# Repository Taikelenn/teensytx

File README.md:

Project in active development, this README will be updated as development progresses

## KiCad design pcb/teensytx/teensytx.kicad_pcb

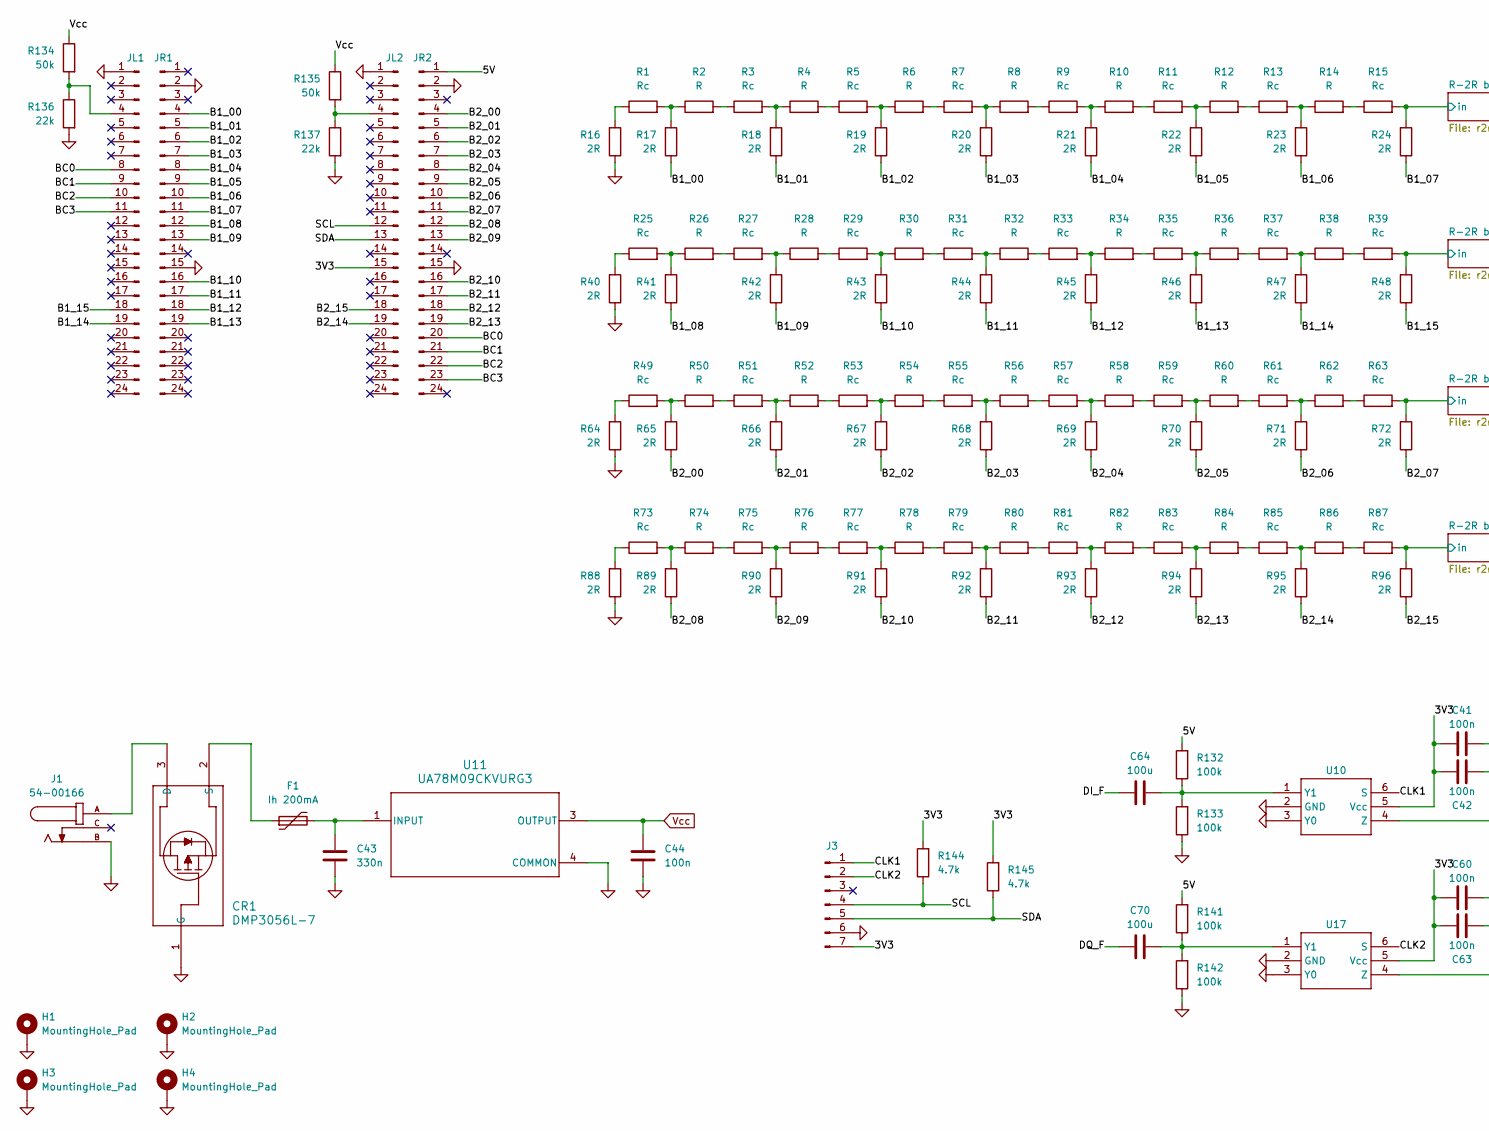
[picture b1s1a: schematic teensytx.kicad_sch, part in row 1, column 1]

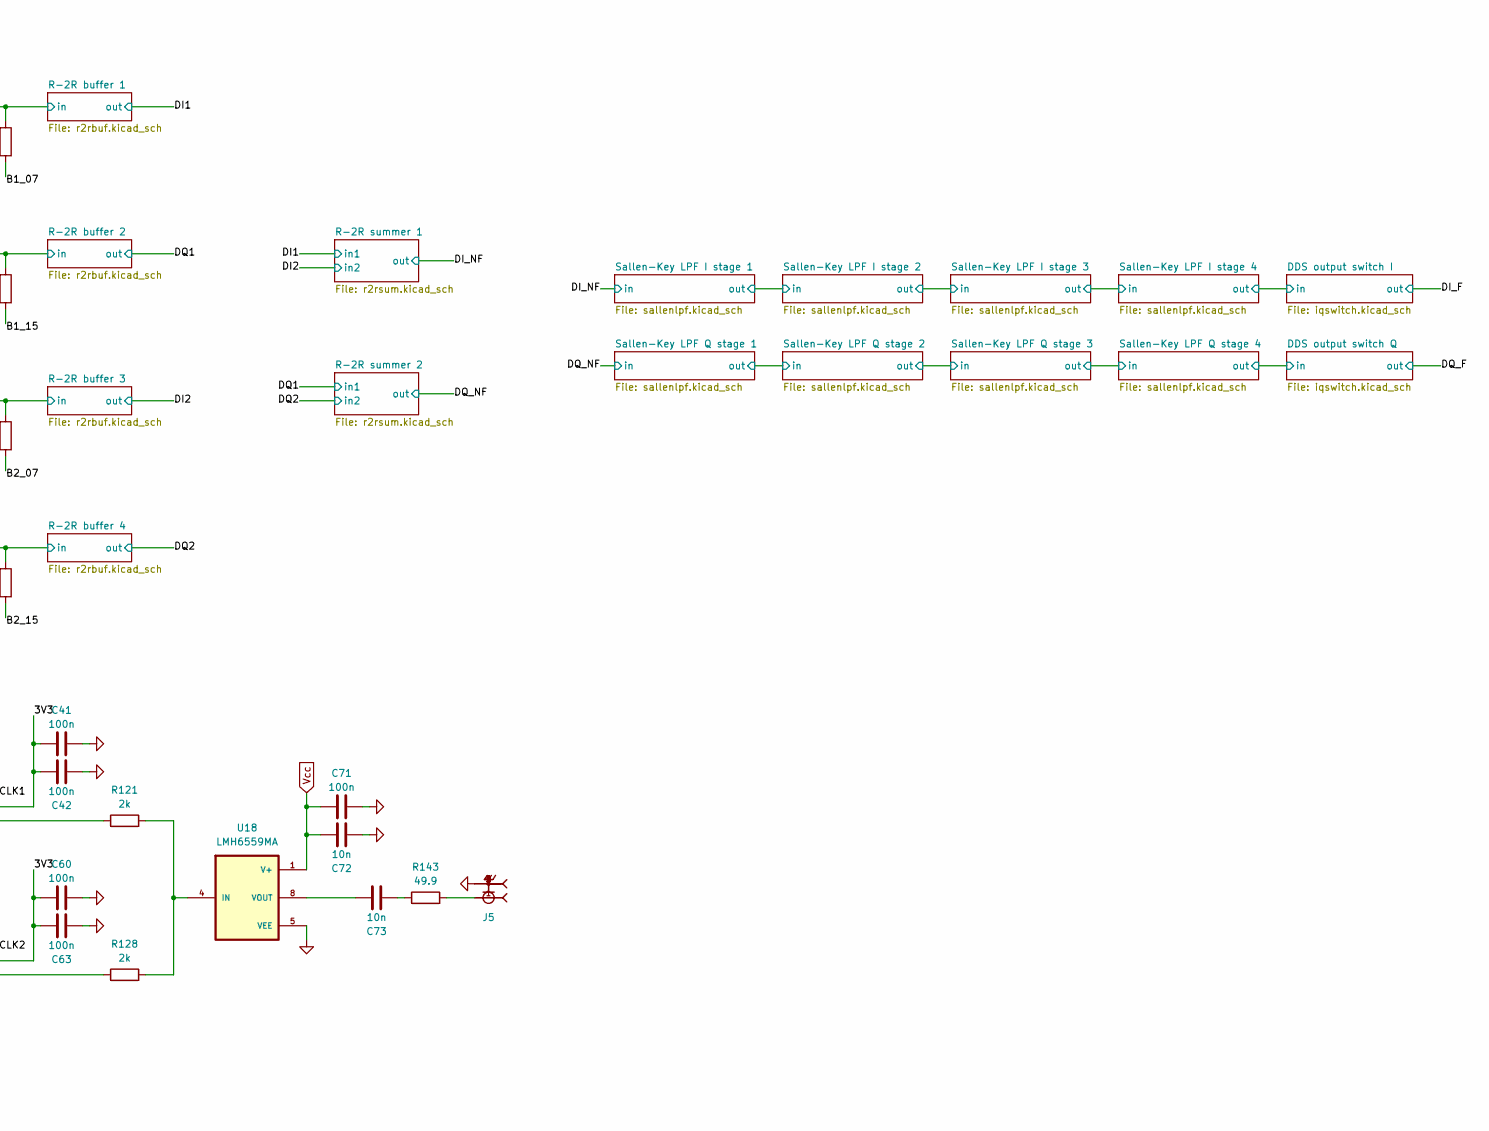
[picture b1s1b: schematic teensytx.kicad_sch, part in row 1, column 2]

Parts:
C41, C42, C44, C60, C63, C71: 100n; C_0805_2012Metric_Pad1.18x1.45mm_HandSolder
C43: 330n; C_0805_2012Metric_Pad1.18x1.45mm_HandSolder
C64, C70: 100u; C_0805_2012Metric_Pad1.18x1.45mm_HandSolder
C72, C73: 10n; C_0805_2012Metric_Pad1.18x1.45mm_HandSolder
CR1: DMP3056L-7; DIODE3_DESD1CAN2SOQ-7_DIO
F1: Ih 200mA; RESC3216X125N
H1, H2, H3, H4: MountingHole_Pad; MountingHole_3.2mm_M3_Pad
J1: 54-00166; TENSILITY_54-00166; PARTREV A
J3: Conn_01x07_Pin; PinHeader_1x07_P2.54mm_Vertical
J5: SMA-J-P-X-RA-TH1; SAMTEC_SMA-J-P-X-RA-TH1; PARTREV K
JL1, JL2: Conn_01x24_Pin; PinHeader_1x24_P2.54mm_Vertical
JR1, JR2: Conn_01x24_Pin; PinHeader_1x24_P2.54mm_Vertical
R1, R3, R5, R7, R9, R11, R13, R15, R25, R27, R29, R31, R33, R35, R37, R39, R49, R51, R53, R55, R57, R59, R61, R63, R73, R75, R77, R79, R81, R83, R85, R87: Rc; R_0805_2012Metric_Pad1.20x1.40mm_HandSolder
R2, R4, R6, R8, R10, R12, R14, R26, R28, R30, R32, R34, R36, R38, R50, R52, R54, R56, R58, R60, R62, R74, R76, R78, R80, R82, R84, R86: R; R_0805_2012Metric_Pad1.20x1.40mm_HandSolder
R16, R17, R18, R19, R20, R21, R22, R23, R24, R40, R41, R42, R43, R44, R45, R46, R47, R48, R64, R65, R66, R67, R68, R69, R70, R71, R72, R88, R89, R90, R91, R92, R93, R94, R95, R96: 2R; R_0805_2012Metric_Pad1.20x1.40mm_HandSolder
R121, R128: 2k; R_0805_2012Metric_Pad1.20x1.40mm_HandSolder
R132, R133, R141, R142: 100k; R_0805_2012Metric_Pad1.20x1.40mm_HandSolder
R134, R135: 50k; R_0805_2012Metric_Pad1.20x1.40mm_HandSolder
R136, R137: 22k; R_0805_2012Metric_Pad1.20x1.40mm_HandSolder
R143: 49.9; R_1206_3216Metric_Pad1.30x1.75mm_HandSolder
R144, R145: 4.7k; R_0805_2012Metric_Pad1.20x1.40mm_HandSolder
U10, U17: TSOP-6_1.65x3.05mm_P0.95mm
U11: UA78M09CKVURG3; KVU0003A_N
U18: LMH6559MA; SOIC127P599X175-8N

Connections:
/3V3: C41.2, C42.2, C60.2, C63.2, J3.7, JL2.15, R144.2, R145.2, U10.5 (Vcc), U17.5 (Vcc)
/5V: JR2.1, R132.2, R141.2
/B1_00: JR1.4, R17.1
/B1_01: JR1.5, R18.1
/B1_02: JR1.6, R19.1
/B1_03: JR1.7, R20.1
/B1_04: JR1.8, R21.1
/B1_05: JR1.9, R22.1
/B1_06: JR1.10, R23.1
/B1_07: JR1.11, R24.1
/B1_08: JR1.12, R41.1
/B1_09: JR1.13, R42.1
/B1_10: JR1.16, R43.1
/B1_11: JR1.17, R44.1
/B1_12: JR1.18, R45.1
/B1_13: JR1.19, R46.1
/B1_14: JL1.19, R47.1
/B1_15: JL1.18, R48.1
/B2_00: JR2.4, R65.1
/B2_01: JR2.5, R66.1
/B2_02: JR2.6, R67.1
/B2_03: JR2.7, R68.1
/B2_04: JR2.8, R69.1
/B2_05: JR2.9, R70.1
/B2_06: JR2.10, R71.1
/B2_07: JR2.11, R72.1
/B2_08: JR2.12, R89.1
/B2_09: JR2.13, R90.1
/B2_10: JR2.16, R91.1
/B2_11: JR2.17, R92.1
/B2_12: JR2.18, R93.1
/B2_13: JR2.19, R94.1
/B2_14: JL2.19, R95.1
/B2_15: JL2.18, R96.1
/BC0: JL1.8, JR2.20
/BC1: JL1.9, JR2.21
/BC2: JL1.10, JR2.22
/BC3: JL1.11, JR2.23
/CLK1: J3.1, U10.6 (S)
/CLK2: J3.2, U17.6 (S)
/DI_F: C64.1; also elsewhere on the board
/DQ_F: C70.1; also elsewhere on the board
/R-2R buffer 1/in: R15.2, R24.2; also elsewhere on the board
/R-2R buffer 2/in: R39.2, R48.2; also elsewhere on the board
/R-2R buffer 3/in: R63.2, R72.2; also elsewhere on the board
/R-2R buffer 4/in: R87.2, R96.2; also elsewhere on the board
/SCL: J3.4, JL2.12, R144.1
/SDA: J3.5, JL2.13, R145.1
GND: C41.1, C42.1, C43.2, C44.2, C60.1, C63.1, C71.2, C72.2, CR1.1 (G), H1.1, H2.1, H3.1, H4.1, J1.B, J3.6, J5.2, J5.3, J5.4, J5.5, JL1.1, JL2.1, JR1.2, JR1.15, JR2.2, JR2.15, R16.1, R40.1, R64.1, R88.1, R133.1, R136.2, R137.2, R142.1, U10.2 (GND), U10.3 (Y0), U11.4 (COMMON), U17.2 (GND), U17.3 (Y0), U18.5 (VEE); also elsewhere on the board
unnamed: C73.2, R143.1
unnamed: CR1.3 (D), J1.A
unnamed: CR1.2 (S), F1.1
unnamed: J5.1, R143.2
unnamed: JL1.4, R134.2, R136.1
unnamed: JL2.4, R135.2, R137.1
unnamed: R1.1, R16.2
unnamed: R1.2, R2.1, R17.2
unnamed: R2.2, R3.1
unnamed: R4.2, R5.1
unnamed: R6.2, R7.1
unnamed: R8.2, R9.1
unnamed: R9.2, R10.1, R21.2
unnamed: R10.2, R11.1
unnamed: R11.2, R12.1, R22.2
unnamed: R12.2, R13.1
unnamed: R13.2, R14.1, R23.2
unnamed: R14.2, R15.1
unnamed: R3.2, R4.1, R18.2
unnamed: R5.2, R6.1, R19.2
unnamed: R7.2, R8.1, R20.2
unnamed: R25.1, R40.2
unnamed: R25.2, R26.1, R41.2
unnamed: R26.2, R27.1
unnamed: R27.2, R28.1, R42.2
unnamed: R28.2, R29.1
unnamed: R29.2, R30.1, R43.2
unnamed: R30.2, R31.1
unnamed: R31.2, R32.1, R44.2
unnamed: R32.2, R33.1
unnamed: R33.2, R34.1, R45.2
unnamed: R34.2, R35.1
unnamed: R35.2, R36.1, R46.2
unnamed: R36.2, R37.1
unnamed: R37.2, R38.1, R47.2
unnamed: R38.2, R39.1
unnamed: R49.1, R64.2
unnamed: R49.2, R50.1, R65.2
unnamed: R50.2, R51.1
unnamed: R51.2, R52.1, R66.2
unnamed: R52.2, R53.1
unnamed: R53.2, R54.1, R67.2
unnamed: R54.2, R55.1
unnamed: R55.2, R56.1, R68.2
unnamed: R56.2, R57.1
unnamed: R57.2, R58.1, R69.2
unnamed: R58.2, R59.1
unnamed: R59.2, R60.1, R70.2
unnamed: R60.2, R61.1
unnamed: R61.2, R62.1, R71.2
unnamed: R62.2, R63.1
unnamed: R73.1, R88.2
unnamed: R73.2, R74.1, R89.2
unnamed: R74.2, R75.1
unnamed: R75.2, R76.1, R90.2
unnamed: R76.2, R77.1
unnamed: R77.2, R78.1, R91.2
unnamed: R78.2, R79.1
unnamed: R79.2, R80.1, R92.2
unnamed: R80.2, R81.1
unnamed: R81.2, R82.1, R93.2
unnamed: R82.2, R83.1
unnamed: R83.2, R84.1, R94.2
unnamed: R84.2, R85.1
unnamed: R85.2, R86.1, R95.2
unnamed: R86.2, R87.1
unnamed: C64.2, R132.1, R133.2, U10.1 (Y1)
unnamed: R121.1, U10.4 (Z)
unnamed: C43.1, F1.2, U11.1 (INPUT)
unnamed: C70.2, R141.1, R142.2, U17.1 (Y1)
unnamed: R128.1, U17.4 (Z)
unnamed: R121.2, R128.2, U18.4 (IN)
unnamed: C73.1, U18.8 (VOUT)
Vcc: C44.1, C71.1, C72.1, R134.1, R135.1, U11.3 (OUTPUT), U18.1 (V+); also elsewhere on the board

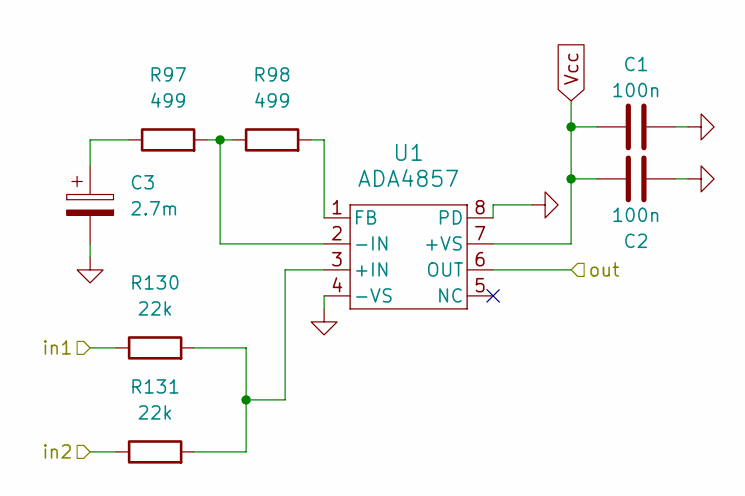
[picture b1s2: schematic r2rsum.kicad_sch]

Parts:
C1, C2: 100n; C_0805_2012Metric_Pad1.18x1.45mm_HandSolder
C3: 2.7m; CP_Radial_D10.0mm_P5.00mm
R97, R98: 499; R_0805_2012Metric_Pad1.20x1.40mm_HandSolder
R130, R131: 22k; R_0805_2012Metric_Pad1.20x1.40mm_HandSolder
U1: ADA4857; R_8_ADI

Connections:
/DI1: R130.1; also elsewhere on the board
/DI2: R131.1; also elsewhere on the board
/DI_NF: U1.6 (OUT); also elsewhere on the board
GND: C1.2, C2.2, C3.2, U1.4 (-VS), U1.8 (PD); also elsewhere on the board
unnamed: C3.1, R97.1
unnamed: R130.2, R131.2, U1.3 (+IN)
unnamed: R97.2, R98.1, U1.2 (-IN)
unnamed: R98.2, U1.1 (FB)
Vcc: C1.1, C2.1, U1.7 (+VS); also elsewhere on the board

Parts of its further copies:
C56, C57: 100n; C_0805_2012Metric_Pad1.18x1.45mm_HandSolder
C58: 2.7m; CP_Radial_D10.0mm_P5.00mm
R124, R125: 499; R_0805_2012Metric_Pad1.20x1.40mm_HandSolder
R139, R140: 22k; R_0805_2012Metric_Pad1.20x1.40mm_HandSolder
U15: ADA4857; R_8_ADI

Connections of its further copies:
/DQ1: R139.1; also elsewhere on the board
/DQ2: R140.1; also elsewhere on the board
/DQ_NF: U15.6 (OUT); also elsewhere on the board
GND: C56.2, C57.2, C58.2, U15.4 (-VS), U15.8 (PD); also elsewhere on the board
unnamed: C58.1, R124.1
unnamed: R139.2, R140.2, U15.3 (+IN)
unnamed: R124.2, R125.1, U15.2 (-IN)
unnamed: R125.2, U15.1 (FB)
Vcc: C56.1, C57.1, U15.7 (+VS); also elsewhere on the board

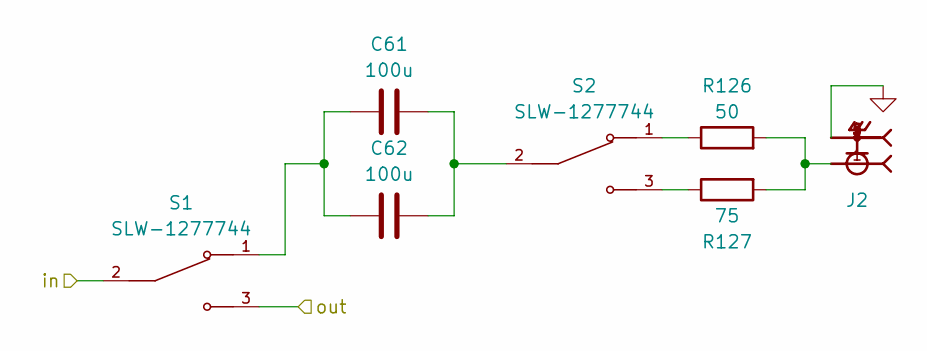
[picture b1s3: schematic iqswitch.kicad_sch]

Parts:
C61, C62: 100u; C_1206_3216Metric_Pad1.33x1.80mm_HandSolder
J2: SMA-J-P-X-RA-TH1; SAMTEC_SMA-J-P-X-RA-TH1; PARTREV K
R126: 50; R_0805_2012Metric_Pad1.20x1.40mm_HandSolder
R127: 75; R_0805_2012Metric_Pad1.20x1.40mm_HandSolder
S1, S2: SLW-1277744; SW_SLW-1277744-3A-N-D; PARTREV 1.01

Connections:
/DDS output switch I/in: S1.2; also elsewhere on the board
/DI_F: S1.3; also elsewhere on the board
GND: J2.2, J2.3, J2.4, J2.5; also elsewhere on the board
unnamed: C61.1, C62.1, S1.1
unnamed: C61.2, C62.2, S2.2
unnamed: J2.1, R126.2, R127.2
unnamed: R126.1, S2.1
unnamed: R127.1, S2.3

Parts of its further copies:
C39, C40: 100u; C_1206_3216Metric_Pad1.33x1.80mm_HandSolder
J4: SMA-J-P-X-RA-TH1; SAMTEC_SMA-J-P-X-RA-TH1; PARTREV K
R113: 50; R_0805_2012Metric_Pad1.20x1.40mm_HandSolder
R120: 75; R_0805_2012Metric_Pad1.20x1.40mm_HandSolder
S5, S6: SLW-1277744; SW_SLW-1277744-3A-N-D; PARTREV 1.01

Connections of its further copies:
/DDS output switch Q/in: S6.2; also elsewhere on the board
/DQ_F: S6.3; also elsewhere on the board
GND: J4.2, J4.3, J4.4, J4.5; also elsewhere on the board
unnamed: C39.1, C40.1, S6.1
unnamed: C39.2, C40.2, S5.2
unnamed: J4.1, R113.2, R120.2
unnamed: R113.1, S5.1
unnamed: R120.1, S5.3

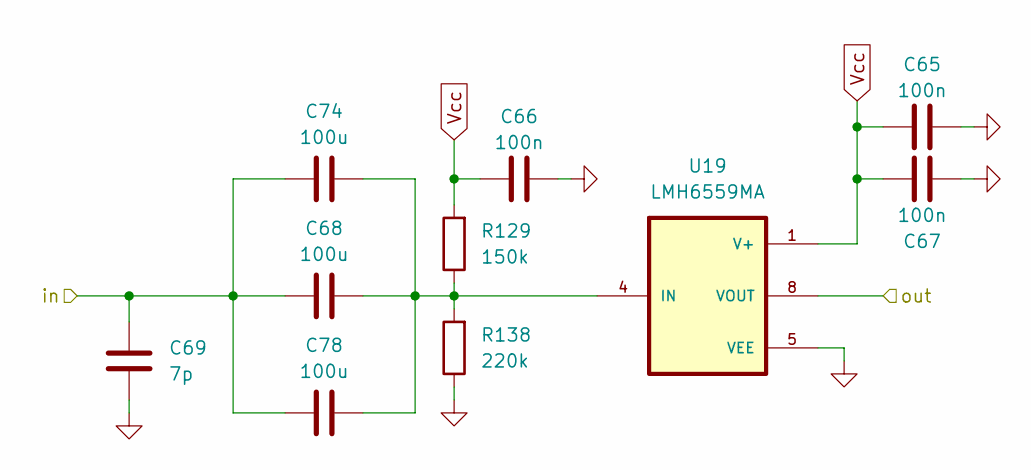
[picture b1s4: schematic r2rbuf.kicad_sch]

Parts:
C65, C66, C67: 100n; C_0805_2012Metric_Pad1.18x1.45mm_HandSolder
C68, C74, C78: 100u; C_1206_3216Metric_Pad1.33x1.80mm_HandSolder
C69: 7p; C_0805_2012Metric_Pad1.18x1.45mm_HandSolder
R129: 150k; R_0805_2012Metric_Pad1.20x1.40mm_HandSolder
R138: 220k; R_0805_2012Metric_Pad1.20x1.40mm_HandSolder
U19: LMH6559MA; SOIC127P599X175-8N

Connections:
/DI1: U19.8 (VOUT); also elsewhere on the board
/R-2R buffer 1/in: C68.1, C69.1, C74.1, C78.1; also elsewhere on the board
GND: C65.2, C66.2, C67.2, C69.2, R138.1, U19.5 (VEE); also elsewhere on the board
unnamed: C68.2, C74.2, C78.2, R129.1, R138.2, U19.4 (IN)
Vcc: C65.1, C66.1, C67.1, R129.2, U19.1 (V+); also elsewhere on the board

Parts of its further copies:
C46, C47, C48, C51, C52, C53: 100n; C_0805_2012Metric_Pad1.18x1.45mm_HandSolder
C49, C54, C75, C76, C77, C79, C80, C81: 100u; C_1206_3216Metric_Pad1.33x1.80mm_HandSolder
C50, C55: 7p; C_0805_2012Metric_Pad1.18x1.45mm_HandSolder
R103, R122: 150k; R_0805_2012Metric_Pad1.20x1.40mm_HandSolder
R104, R123: 220k; R_0805_2012Metric_Pad1.20x1.40mm_HandSolder
U20, U21, U22: LMH6559MA; SOIC127P599X175-8N

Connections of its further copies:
/DI2: U21.8 (VOUT); also elsewhere on the board
/DQ1: U20.8 (VOUT); also elsewhere on the board
/DQ2: U22.8 (VOUT); also elsewhere on the board
/R-2R buffer 2/in: C75.1, C79.1; also elsewhere on the board
/R-2R buffer 3/in: C49.1, C50.1, C76.1, C80.1; also elsewhere on the board
/R-2R buffer 4/in: C54.1, C55.1, C77.1, C81.1; also elsewhere on the board
GND: C46.2, C47.2, C48.2, C50.2, C51.2, C52.2, C53.2, C55.2, R104.1, R123.1, U20.5 (VEE), U21.5 (VEE), U22.5 (VEE); also elsewhere on the board
unnamed: C75.2, C79.2, U20.4 (IN)
unnamed: C49.2, C76.2, C80.2, R103.1, R104.2, U21.4 (IN)
unnamed: C54.2, C77.2, C81.2, R122.1, R123.2, U22.4 (IN)
Vcc: C46.1, C47.1, C48.1, C51.1, C52.1, C53.1, R103.2, R122.2, U20.1 (V+), U21.1 (V+), U22.1 (V+); also elsewhere on the board

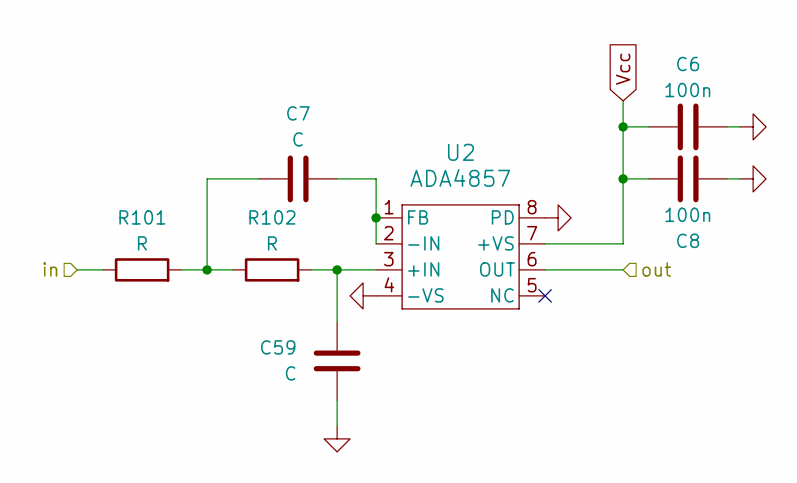
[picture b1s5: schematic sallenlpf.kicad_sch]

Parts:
C6, C8: 100n; C_0805_2012Metric_Pad1.18x1.45mm_HandSolder
C7, C59: C; C_0805_2012Metric_Pad1.18x1.45mm_HandSolder
R101, R102: R; R_0805_2012Metric_Pad1.20x1.40mm_HandSolder
U2: ADA4857; R_8_ADI

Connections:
/DI_NF: R101.1; also elsewhere on the board
/Sallen-Key LPF I stage 1/out: U2.6 (OUT); also elsewhere on the board
GND: C6.2, C8.2, C59.2, U2.4 (-VS), U2.8 (PD); also elsewhere on the board
unnamed: C7.1, R101.2, R102.1
unnamed: C59.1, R102.2, U2.3 (+IN)
unnamed: C7.2, U2.1 (FB), U2.2 (-IN)
Vcc: C6.1, C8.1, U2.7 (+VS); also elsewhere on the board

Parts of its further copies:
C11, C13, C15, C17, C19, C21, C23, C25, C27, C29, C31, C33, C35, C37: 100n; C_0805_2012Metric_Pad1.18x1.45mm_HandSolder
C12, C14, C16, C18, C20, C22, C24, C26, C28, C30, C32, C34, C36, C38: C; C_0805_2012Metric_Pad1.18x1.45mm_HandSolder
R105, R106, R107, R108, R109, R110, R111, R112, R114, R115, R116, R117, R118, R119: R; R_0805_2012Metric_Pad1.20x1.40mm_HandSolder
U3, U4, U5, U6, U7, U8, U9: ADA4857; R_8_ADI

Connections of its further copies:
/DDS output switch I/in: U5.6 (OUT); also elsewhere on the board
/DDS output switch Q/in: U9.6 (OUT); also elsewhere on the board
/DQ_NF: R111.1; also elsewhere on the board
/Sallen-Key LPF I stage 1/out: R105.1; also elsewhere on the board
/Sallen-Key LPF I stage 2/out: R107.1, U3.6 (OUT)
/Sallen-Key LPF I stage 3/out: R109.1, U4.6 (OUT)
/Sallen-Key LPF Q stage 1/out: R114.1, U6.6 (OUT)
/Sallen-Key LPF Q stage 2/out: R116.1, U7.6 (OUT)
/Sallen-Key LPF Q stage 3/out: R118.1, U8.6 (OUT)
GND: C11.2, C13.2, C14.2, C15.2, C17.2, C18.2, C19.2, C21.2, C22.2, C23.2, C25.2, C26.2, C27.2, C29.2, C30.2, C31.2, C33.2, C34.2, C35.2, C37.2, C38.2, U3.4 (-VS), U3.8 (PD), U4.4 (-VS), U4.8 (PD), U5.4 (-VS), U5.8 (PD), U6.4 (-VS), U6.8 (PD), U7.4 (-VS), U7.8 (PD), U8.4 (-VS), U8.8 (PD), U9.4 (-VS), U9.8 (PD); also elsewhere on the board
unnamed: C12.1, R105.2, R106.1
unnamed: C16.1, R107.2, R108.1
unnamed: C20.1, R109.2, R110.1
unnamed: C24.1, R111.2, R112.1
unnamed: C28.1, R114.2, R115.1
unnamed: C32.1, R116.2, R117.1
unnamed: C36.1, R118.2, R119.1
unnamed: C14.1, R106.2, U3.3 (+IN)
unnamed: C12.2, U3.1 (FB), U3.2 (-IN)
unnamed: C18.1, R108.2, U4.3 (+IN)
unnamed: C16.2, U4.1 (FB), U4.2 (-IN)
unnamed: C22.1, R110.2, U5.3 (+IN)
unnamed: C20.2, U5.1 (FB), U5.2 (-IN)
unnamed: C26.1, R112.2, U6.3 (+IN)
unnamed: C24.2, U6.1 (FB), U6.2 (-IN)
unnamed: C30.1, R115.2, U7.3 (+IN)
unnamed: C28.2, U7.1 (FB), U7.2 (-IN)
unnamed: C34.1, R117.2, U8.3 (+IN)
unnamed: C32.2, U8.1 (FB), U8.2 (-IN)
unnamed: C38.1, R119.2, U9.3 (+IN)
unnamed: C36.2, U9.1 (FB), U9.2 (-IN)
Vcc: C11.1, C13.1, C15.1, C17.1, C19.1, C21.1, C23.1, C25.1, C27.1, C29.1, C31.1, C33.1, C35.1, C37.1, U3.7 (+VS), U4.7 (+VS), U5.7 (+VS), U6.7 (+VS), U7.7 (+VS), U8.7 (+VS), U9.7 (+VS); also elsewhere on the board

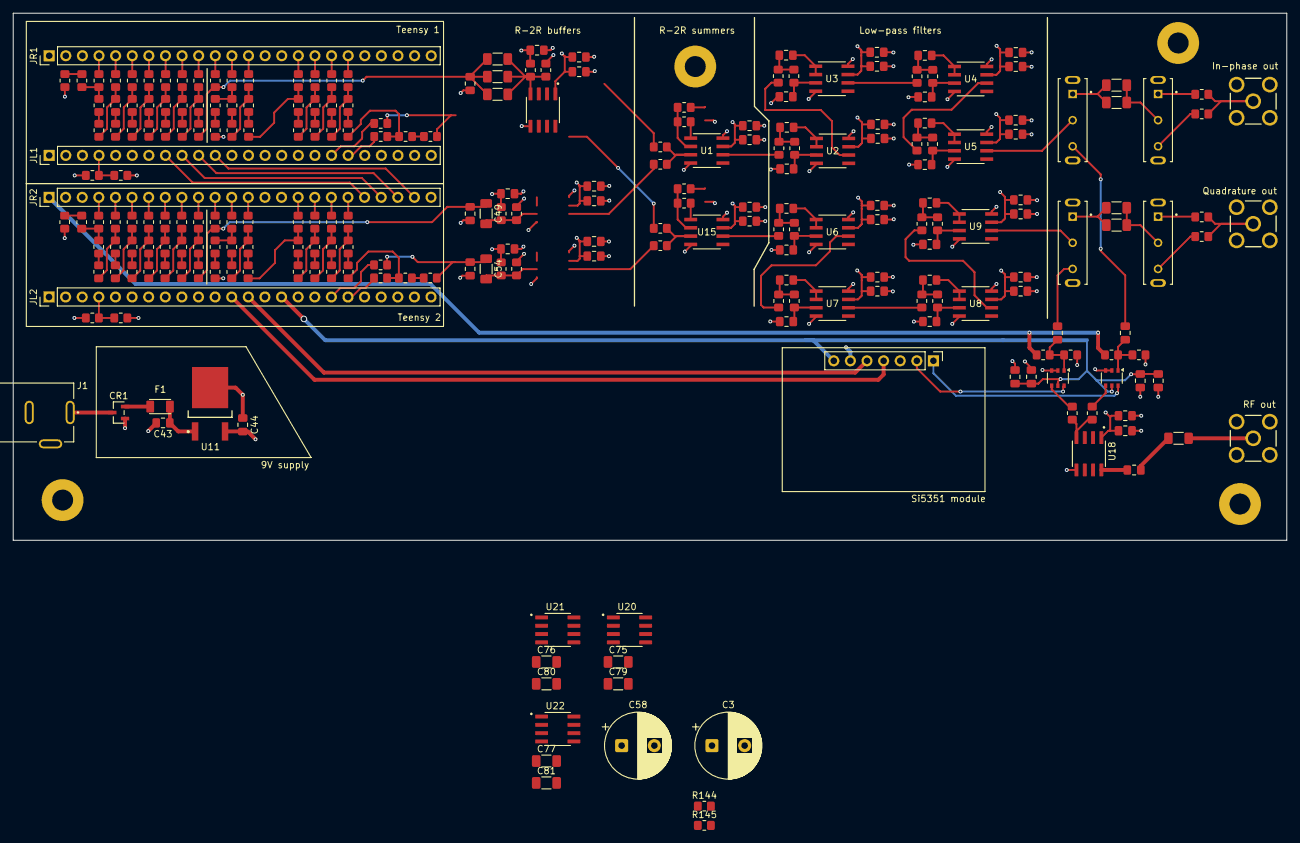
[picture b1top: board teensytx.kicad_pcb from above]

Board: 4 copper layers, 194.8 x 80.6 mm, 256 parts (0 on the bottom side), 183 nets.
